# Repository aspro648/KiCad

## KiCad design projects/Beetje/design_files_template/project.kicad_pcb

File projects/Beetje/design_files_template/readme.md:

Beetje Blok Template

Project website: https://hackaday.io/project/160638-beetje-bloks

Bill Of Materials
----------------
  
- 1 ea., Perfect Purple PCB from OSH Park, with not so perfect layout from [project.kicad_pcb](project.kicad_pcb) file.
- 1 ea., C1 CAP CER 0.1UF 50V X7R 0805, https://www.digikey.com/short/j58qjp
- 1 ea., D1 LED 0603 SMD https://www.digikey.com/short/j5h3h5
- 1 ea., R1 1K 0603 SMD Resistor, https://www.digikey.com/short/jfhzq7
- 1 ea., SW1 TACTILE KMR231NG LFS, https://www.digikey.com/short/jb2r5m

Optional

- 1 ea., CONN HEADER .100" SNGL STR 40POS, https://www.digikey.com/short/jfcn42
- J2, CONN HEADER FEMALE 6POS .1" GOLD, https://www.digikey.com/short/jfcnz3
- J4, CONN HEADER FEMALE 8POS .1" GOLD, https://www.digikey.com/short/jfcnzj

License
----------------
[Attribution-ShareAlike 3.0 United States (CC BY-SA 3.0 US)](https://creativecommons.org/licenses/by-sa/3.0/us/)

You are free to:

- Share — copy and redistribute the material in any medium or format
- Adapt — remix, transform, and build upon the material

Under the following terms:

- Attribution — You must give appropriate credit, provide a link to the license, and indicate if changes were made. You may do so in any reasonable manner, but not in any way that suggests the licensor endorses you or your use.
- ShareAlike — If you remix, transform, or build upon the material, you must distribute your contributions under the same license as the original.

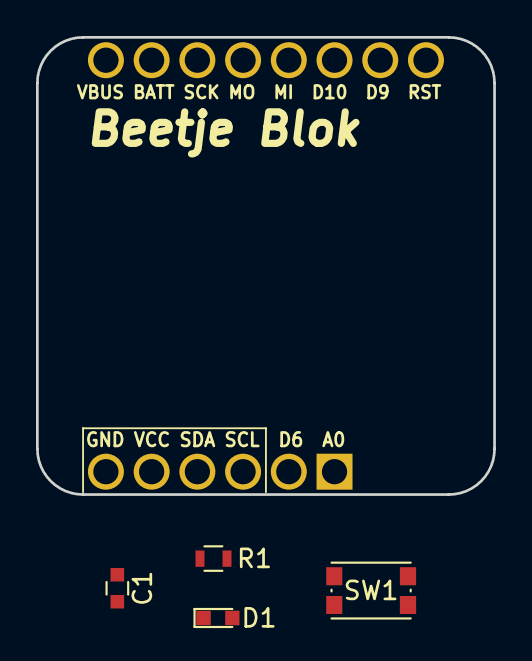
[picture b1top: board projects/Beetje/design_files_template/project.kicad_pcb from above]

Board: 2 copper layers, 25.4 x 25.4 mm, 7 parts (0 on the bottom side), 3 nets, no tracks yet.

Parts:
C1: 0.1uF; C_0603
D1: LED; LED_0603
J2: Beetje_Bottom
J4: Beetje_Top
R1: 1K; R_0603
SW1: SW_Push; SW_SPST_KMR2
VAL: MadeInOregonRev25

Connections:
GND: C1.2, J4.7, R1.1, SW1.2
unnamed: D1.1, R1.2
VCC: C1.1, J4.6

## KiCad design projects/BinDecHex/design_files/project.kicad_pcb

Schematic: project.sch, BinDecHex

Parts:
D0, D1, D2, D3, D4, D5, D6, D7: LED; LED-3MM
LS1: Speaker; PS1240_piezo
Q1, Q2, Q3: 2N3904; TO-92_NPN_EBC_wide
R0, R1, R2, R3, R4, R5, R6, R7: 470; Resistor_Horz
R8, R9, R10: 100; Resistor_Horz
R11: 10K; Resistor_Horz
SHIELD1: ARDUINO_SHIELD
SW1, SW2, SW3: SW_PUSHBUTTON; SW_PUSH_SMALL
SW4, SW5, SW6: SW_SPST; SW_Micro_SPST
U1: 74HC595; DIP-16_W7.62mm
U2, U3: 7SEGMENT_CC; 7SegmentLED_LTS6760_LTS6780

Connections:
+5V: R11.2, SHIELD1.5V, U1.10, U1.16
GND: LS1.2, Q1.1, Q2.1, Q3.1, SHIELD1.GND1, SHIELD1.GND2, SHIELD1.GND3, SW1.1, SW2.1, SW3.1, SW4.2, SW5.2, SW6.2, U1.8
unnamed: D0.1 (K), D1.1 (K), D2.1 (K), D3.1 (K), D4.1 (K), D5.1 (K), D6.1 (K), D7.1 (K), Q3.3
unnamed: D0.2 (A), R0.1, U2.7, U3.7
unnamed: D1.2 (A), R1.1, U2.6, U3.6
unnamed: D2.2 (A), R2.1, U2.4, U3.4
unnamed: D3.2 (A), R3.1, U2.2, U3.2
unnamed: D4.2 (A), R4.1, U2.1, U3.1
unnamed: D5.2 (A), R5.1, U2.9, U3.9
unnamed: D6.2 (A), R6.1, U2.10, U3.10
unnamed: D7.2 (A), R7.1, U2.5, U3.5
unnamed: LS1.1, SHIELD1.7
unnamed: Q1.2, R8.1
unnamed: Q1.3, U2.3, U2.8
unnamed: Q2.2, R9.1
unnamed: Q2.3, U3.3, U3.8
unnamed: Q3.2, R10.1
unnamed: R0.2, U1.15
unnamed: R1.2, U1.1
unnamed: R2.2, U1.2
unnamed: R3.2, U1.3
unnamed: R4.2, U1.4
unnamed: R5.2, U1.5
unnamed: R6.2, U1.6
unnamed: R7.2, U1.7
unnamed: R8.2, SHIELD1.4
unnamed: R9.2, SHIELD1.3
unnamed: R10.2, SHIELD1.2
unnamed: R11.1, U1.13
unnamed: SHIELD1.8, U1.12
unnamed: SHIELD1.9, U1.11
unnamed: SHIELD1.10, U1.14
unnamed: SHIELD1.11, SW4.1
unnamed: SHIELD1.12, SW5.1
unnamed: SHIELD1.13, SW6.1
unnamed: SHIELD1.AD1, SW1.2
unnamed: SHIELD1.AD2, SW2.2
unnamed: SHIELD1.AD3, SW3.2

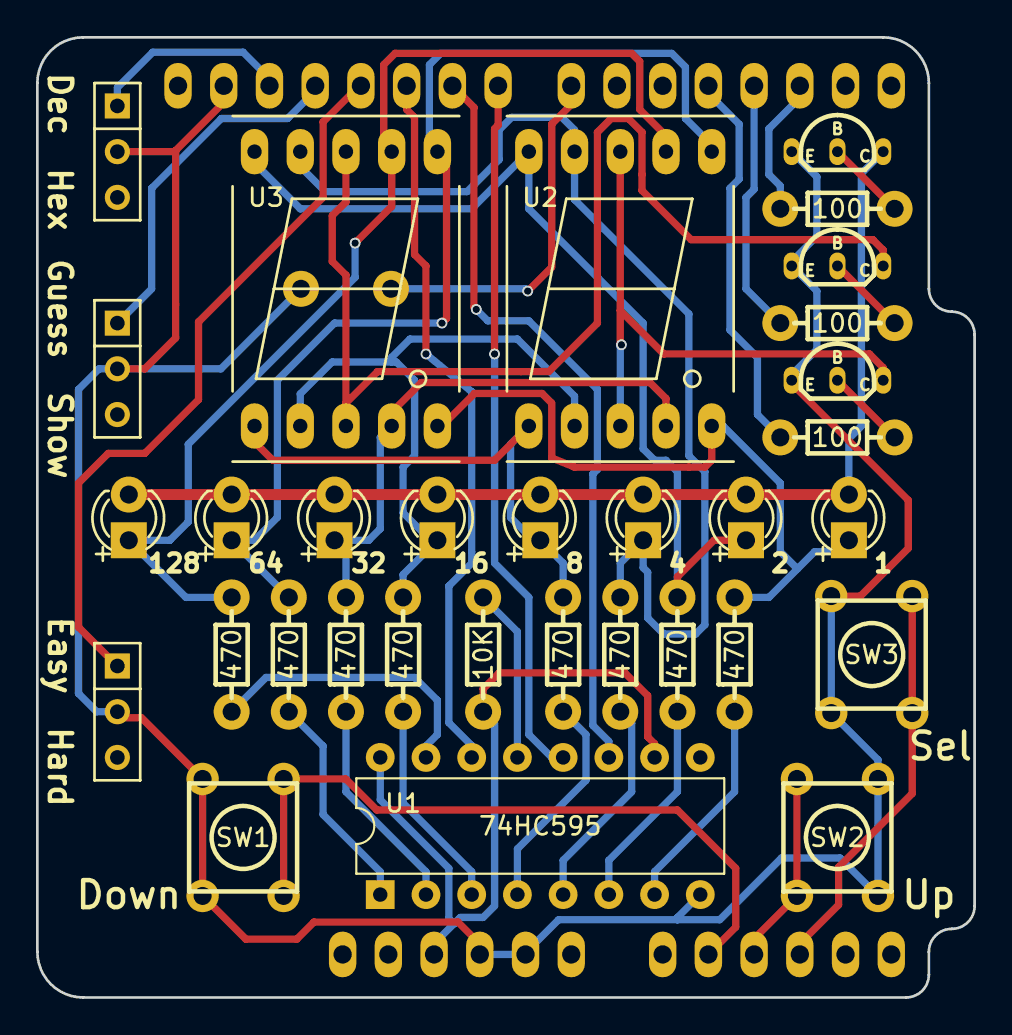
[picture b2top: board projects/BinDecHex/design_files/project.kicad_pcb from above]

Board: 2 copper layers, 52.1 x 53.3 mm, 36 parts (1 on the bottom side), 38 nets.

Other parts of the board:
VAL: MB225rev
VAL#2: MadeInOregonRev25

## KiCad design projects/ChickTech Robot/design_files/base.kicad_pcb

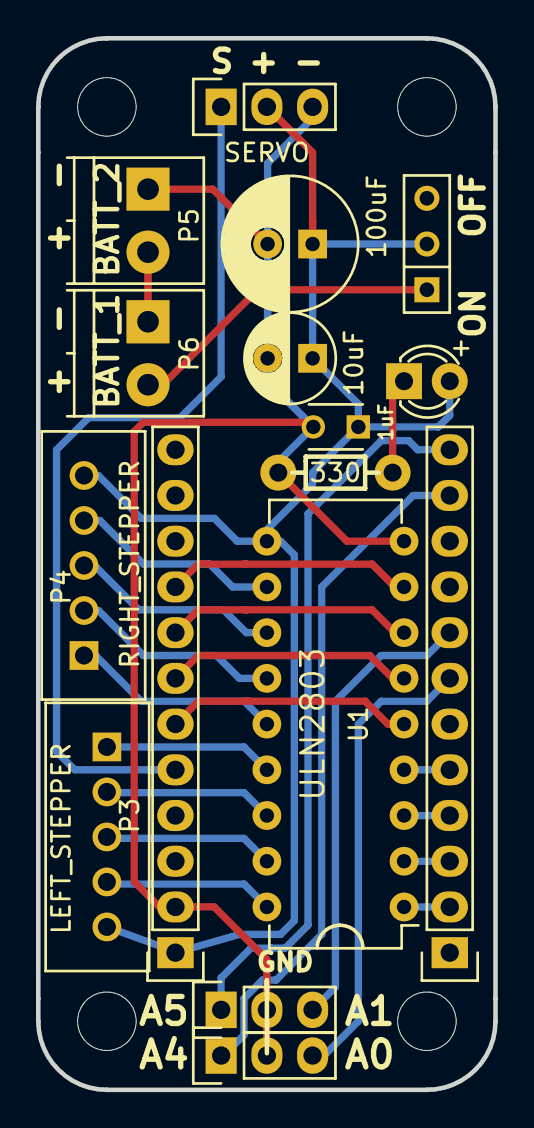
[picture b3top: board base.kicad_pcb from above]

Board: 2 copper layers, 25.4 x 58.4 mm, 22 parts (0 on the bottom side), 26 nets.

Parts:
C1: 100uF; C_Radial_D7.5_L11.2_P2.5
C2: 10uF; C_Radial_D5_L11_P2.5
C3: 1uF; C_Disc_D3_P2.5
D1: LED; LED-3MM
P1: TRINKET_LEFT; Pin_Header_Straight_1x12
P2: TRINKET_RIGHT; Pin_Header_Straight_1x12
P3: LEFT_STEPPER; JST_B5B-XH-A
P4: RIGHT_STEPPER; JST_B5B-XH-A
P5: BATT1; TerminalBlock_Pheonix_PT-3.5mm_2pol
P6: BATT2; TerminalBlock_Pheonix_PT-3.5mm_2pol
P7: SERVO; Pin_Header_Straight_1x03
P8: A5 - A1; Pin_Header_Straight_1x03
P9, P9#2, P9#3, P9#4: CONN_01X01; Lego_Pad
P11: A4 - A0; Pin_Header_Straight_1x03
R1: 330; Resistor_Horz
SW1: SPST; SW_Micro_SPST
U1: ULN2803; DIP-18_W7.62mm
VAL: MadeInOregonRev25
VAL#2: MB225rev

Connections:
/A0: P1.7, P11.3
/A1: P1.8, P8.3
/A4: P1.11, P11.1
/A5: P1.12, P8.1
/D3: P2.9, U1.8
/D4: P2.8, U1.7
/D5: P2.7, U1.6
/D6: P2.6, U1.5
/D8: P2.5, P7.1
/D10: P1.2, U1.1
/D11: P1.3, U1.2
/D12: P1.4, U1.3
/D13: P1.5, U1.4
/VBAT: C1.1, C2.1, C3.1, D1.2, P2.1, P3.5, P4.5, P7.2, SW1.2, U1.10
GND: C1.2, C2.2, C3.2, P2.2, P5.1, P7.3, P8.2, P11.2, R1.2, U1.9
unnamed: D1.1, R1.1
unnamed: P3.1, U1.15
unnamed: P3.2, U1.16
unnamed: P3.3, U1.17
unnamed: P3.4, U1.18
unnamed: P4.1, U1.14
unnamed: P4.2, U1.13
unnamed: P4.3, U1.12
unnamed: P4.4, U1.11
unnamed: P5.2, P6.1
unnamed: P6.2, SW1.1

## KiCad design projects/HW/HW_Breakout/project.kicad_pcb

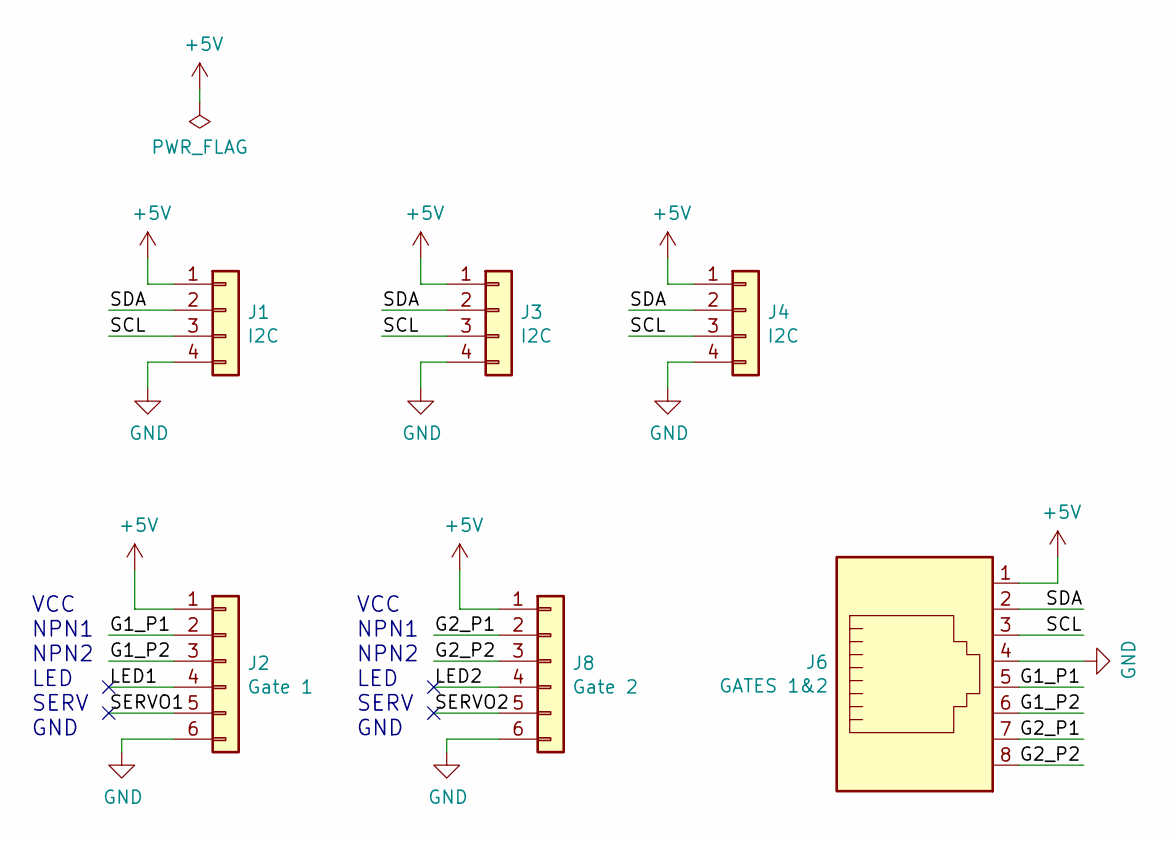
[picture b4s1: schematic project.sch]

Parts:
J1: I2C; PinSocket_2x02_P2.54mm_Vertical
J2: Gate 1; Molex_PicoBlade_53048-0610_1x06_P1.25mm_Horizontal
J3, J4: I2C; 4P4C_narrow
J6: GATES 1&2; RJ45_Amphenol_54602-x08_Horizontal
J8: Gate 2; Molex_PicoBlade_53048-0610_1x06_P1.25mm_Horizontal

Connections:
+5V: J1.1, J2.1, J3.1, J4.1, J6.1, J8.1
/G1_P1: J2.2, J6.5
/G1_P2: J2.3, J6.6
/G2_P1: J6.7, J8.2
/G2_P2: J6.8, J8.3
/LED1: J2.4
/LED2: J8.4
/SCL: J1.3, J3.3, J4.3, J6.3
/SDA: J1.2, J3.2, J4.2, J6.2
/SERVO1: J2.5
/SERVO2: J8.5
GND: J1.4, J2.6, J3.4, J4.4, J6.4, J8.6

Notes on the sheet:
VCC NPN1 NPN2 LED SERV GND

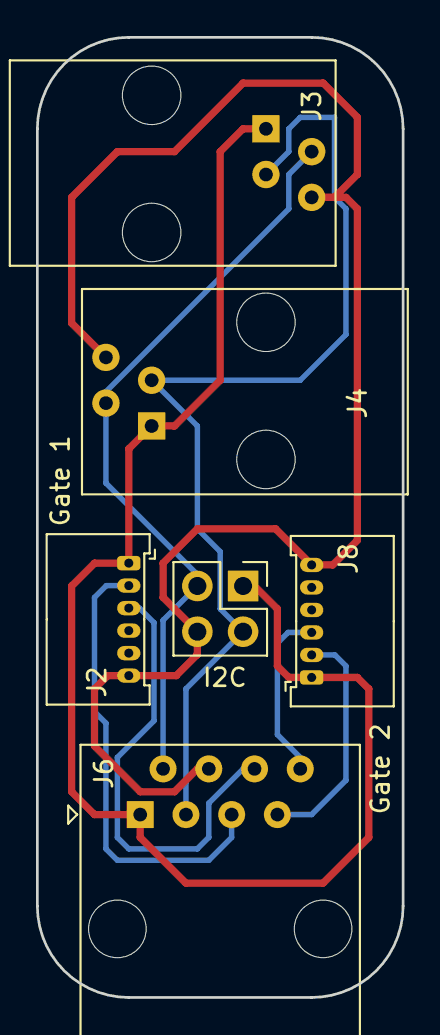
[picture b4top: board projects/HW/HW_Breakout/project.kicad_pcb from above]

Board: 2 copper layers, 20.3 x 53.3 mm, 6 parts (0 on the bottom side), 8 nets.

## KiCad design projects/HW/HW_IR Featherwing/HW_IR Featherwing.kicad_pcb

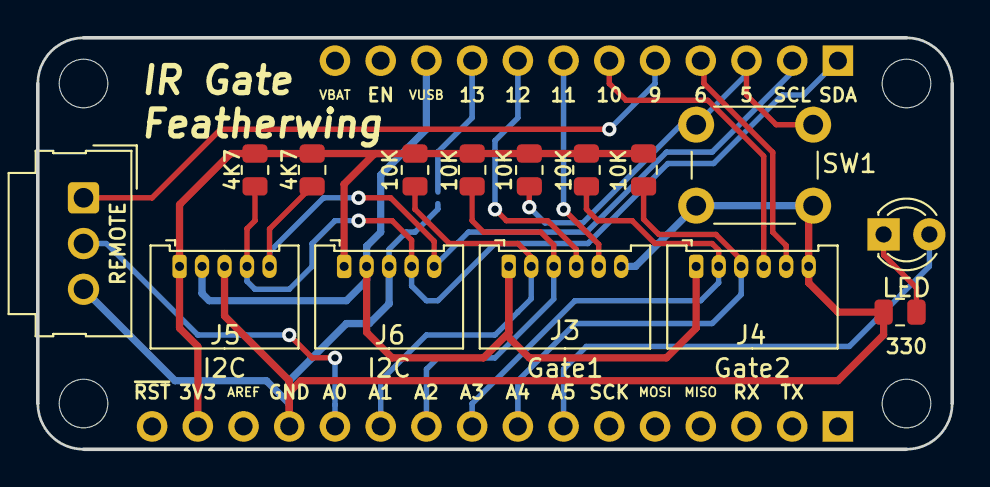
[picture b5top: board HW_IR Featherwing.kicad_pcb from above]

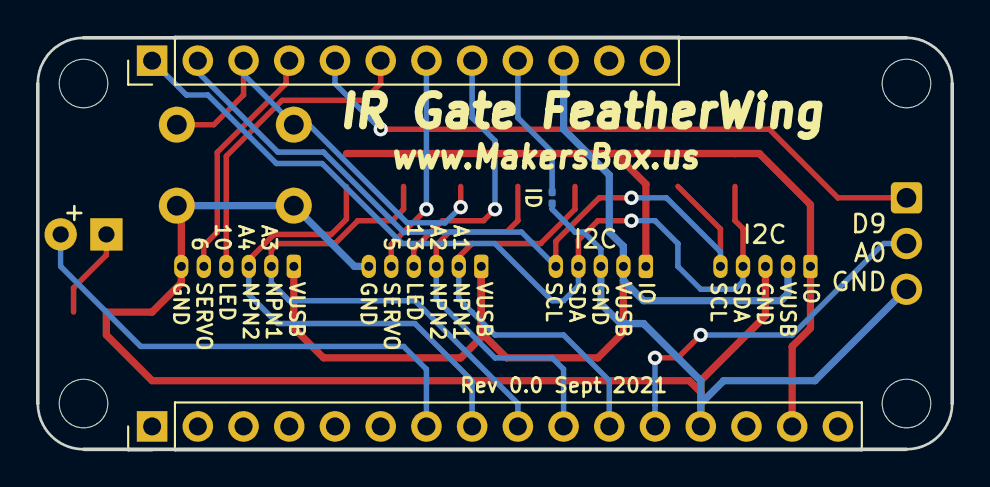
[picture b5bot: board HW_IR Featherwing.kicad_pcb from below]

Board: 2 copper layers, 50.8 x 22.9 mm, 18 parts (3 on the bottom side), 19 nets.

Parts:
D1: LED; LED_D3.0mm
J1: feather long; PinHeader_1x16_P2.54mm_Vertical
J2: feather short; PinHeader_1x12_P2.54mm_Vertical
J3: Gate1; Molex_PicoBlade_53048-0610_1x06_P1.25mm_Horizontal
J4: Gate2; Molex_PicoBlade_53048-0610_1x06_P1.25mm_Horizontal
J5, J6: I2C; Molex_PicoBlade_53048-0510_1x05_P1.25mm_Horizontal
J7: REMOTE; Molex_SL_171971-0003_1x03_P2.54mm_Vertical
JP1: ID; R_0201_0603Metric
R1, R2: 4K7; R_0805_2012Metric
R3: 330; R_0805_2012Metric
R4, R5, R6, R7, R8: 10K; R_0805_2012Metric
SW1: SW_Push; SW_PUSH_6mm

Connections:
+3V3: J1.15, J5.1, J6.1, R1.2, R2.2, R4.2, R5.2, R6.2, R7.2, R8.2
/5: J2.3, R4.1, SW1.1
/6: J2.4, J4.5
/9: J2.5, J7.1
/10: J2.6, J4.4
/11: J2.7, J3.5
/12: J2.8, J3.4
/13: J2.9, JP1.1
/A0: J1.12, J7.2
/A1: J1.11, J3.2, R6.1
/A2: J1.10, J3.3, R5.1
/A3: J1.9, J4.2, R8.1
/A4: J1.8, J4.3, R7.1
/A5: D1.2, J1.7
/SCL: J2.2, J5.5, J6.5, R1.1
/SDA: J2.1, J5.4, J6.4, R2.1
/VUSB: J2.10, J3.1, J4.1, J5.2, J6.2
GND: J1.13, J3.6, J4.6, J5.3, J6.3, J7.3, JP1.2, R3.2, SW1.2
unnamed: D1.1, R3.1

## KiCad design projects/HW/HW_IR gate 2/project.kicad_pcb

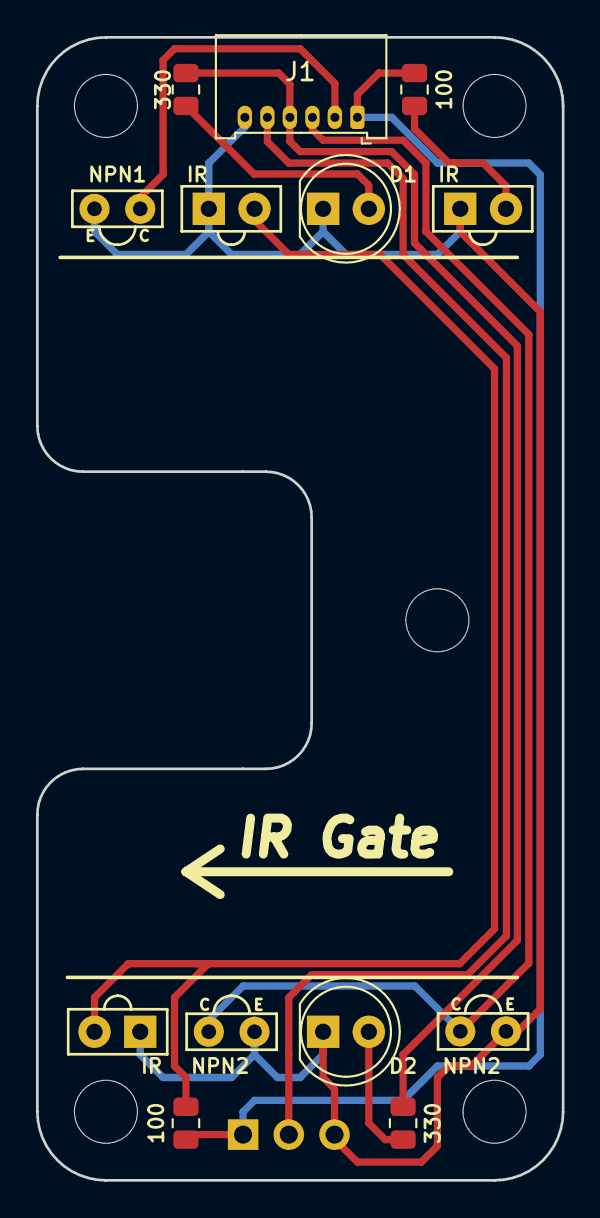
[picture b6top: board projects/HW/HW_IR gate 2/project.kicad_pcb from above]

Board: 2 copper layers, 29.2 x 63.5 mm, 15 parts (1 on the bottom side), 10 nets.

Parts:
D1, D2: LED; LED_D5.0mm
D3, D7, D8: IR; IR_LED
J1: Gate; Molex_PicoBlade_53048-0610_1x06_P1.25mm_Horizontal
J2: SERVO; PinHeader_1x03_P2.54mm_Vertical
Q1: NPN1; PHOTOTRANS
Q2, Q3: NPN2; PHOTOTRANS
R10, R11: 100; R_0805_2012Metric
R13, R14: 330; R_0805_2012Metric
VAL: MadeInOregonRev25

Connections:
/LED: J1.4, R13.2, R14.2
/NPN1: J1.2, Q1.1
/NPN2: J1.3, Q2.1, Q3.1
/SERVO: J1.5, J2.2
GND: D1.1, D2.1, D3.1, D7.1, D8.1, J1.6, J2.3, Q1.2, Q2.2, Q3.2
unnamed: D1.2, R14.1
unnamed: D2.2, R13.1
unnamed: D3.2, D7.2, R11.1
unnamed: D8.2, R10.1
VCC: J1.1, J2.1, R10.2, R11.2

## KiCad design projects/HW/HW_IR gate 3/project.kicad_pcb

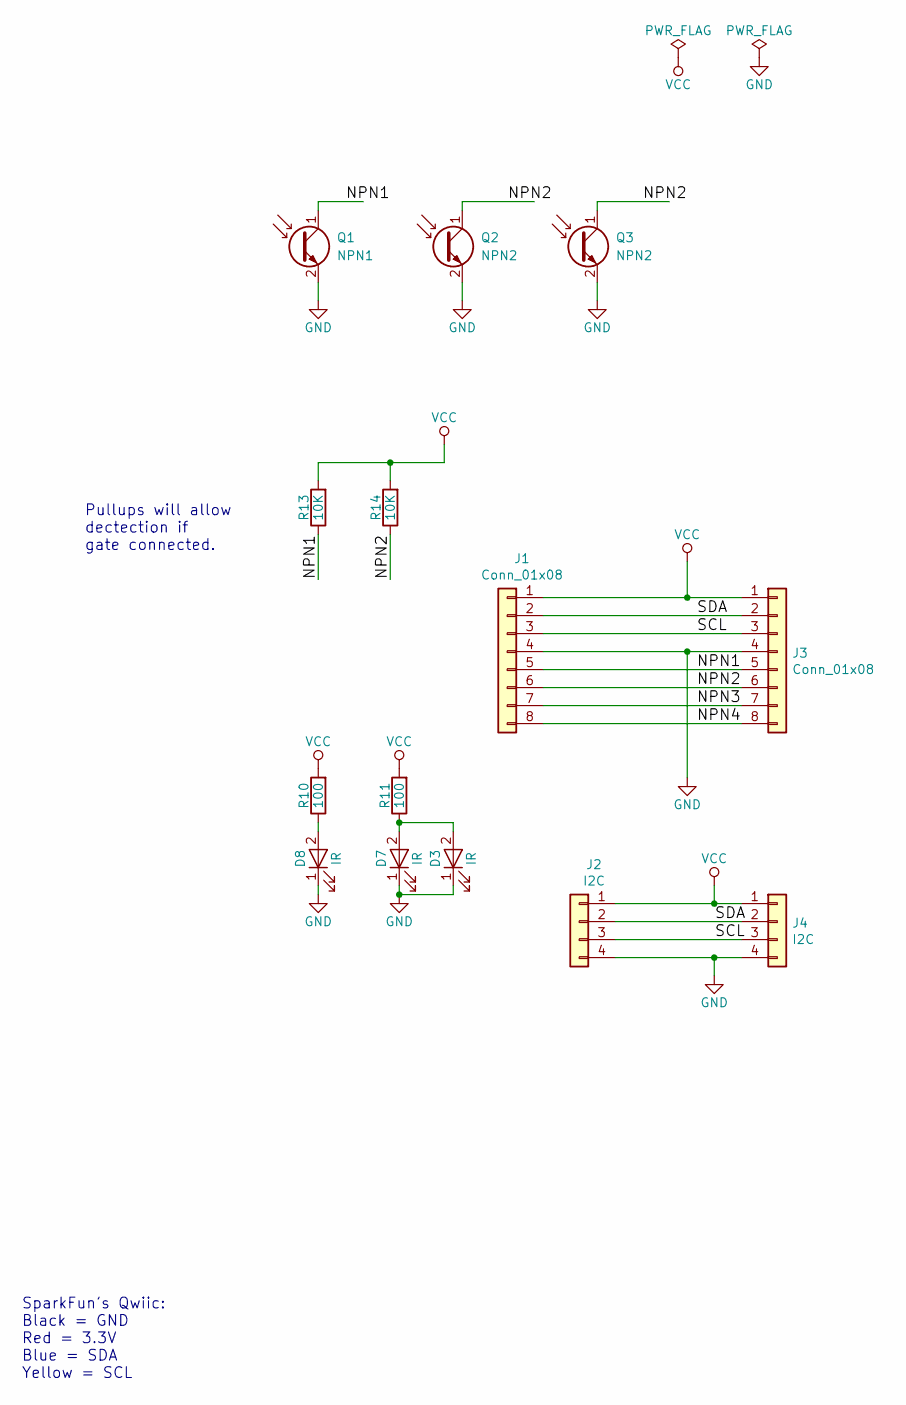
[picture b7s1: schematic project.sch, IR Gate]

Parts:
D3, D7, D8: IR; IR_LED
J1, J3: Conn_01x08; Molex_PicoBlade_53048-0810_1x08_P1.25mm_Horizontal
J2, J4: I2C; Molex_PicoBlade_53048-0410_1x04_P1.25mm_Horizontal
Q1: NPN1; PHOTOTRANS
Q2, Q3: NPN2; PHOTOTRANS
R10, R11: 100; R_Axial_DIN0204_L3.6mm_D1.6mm_P5.08mm_Horizontal
R13, R14: 10K; R_Axial_DIN0204_L3.6mm_D1.6mm_P5.08mm_Horizontal

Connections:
/NPN1: J1.5, J3.5, Q1.1 (C), R13.1
/NPN2: J1.6, J3.6, Q2.1 (C), Q3.1 (C), R14.1
/NPN3: J1.7, J3.7
/NPN4: J1.8, J3.8
/SCL: J1.3, J2.3, J3.3, J4.3
/SDA: J1.2, J2.2, J3.2, J4.2
GND: D3.1 (K), D7.1 (K), D8.1 (K), J1.4, J2.4, J3.4, J4.4, Q1.2 (E), Q2.2 (E), Q3.2 (E)
unnamed: D3.2 (A), D7.2 (A), R11.1
unnamed: D8.2 (A), R10.1
VCC: J1.1, J2.1, J3.1, J4.1, R10.2, R11.2, R13.2, R14.2

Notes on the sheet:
SparkFun's Qwiic: Black = GND Red = 3.3V Blue = SDA Yellow = SCL
Pullups will allow dectection if gate connected.

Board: 2 copper layers, 15 parts (0 on the bottom side), 10 nets, no tracks yet.

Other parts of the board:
VAL: MadeInOregonRev25
